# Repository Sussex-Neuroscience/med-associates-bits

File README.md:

# Med Associates open source add ons and bits

 Med Associates sells a number of tools for behavioural systems. This commercial system is a complete solution for behavioural experiments, and can be used to run multiple behavioural boxes in parallel. It is unfortunately rather expensive and closed source, so users are almost always dependent on MedAssociates for upgrades and customization (and whenever something breaks). Another downside is that an unusual 28V system is employed, so adding/customizing things has an extra layer of complexity.

 This repository is a collection of bits, add-ons and some knowledge on the system we have gathered over the years.
 
### [License](./LICENSE)

### [Code of Conduct](./code_of_conduct.md)

### [Contributing](./contributing.md)

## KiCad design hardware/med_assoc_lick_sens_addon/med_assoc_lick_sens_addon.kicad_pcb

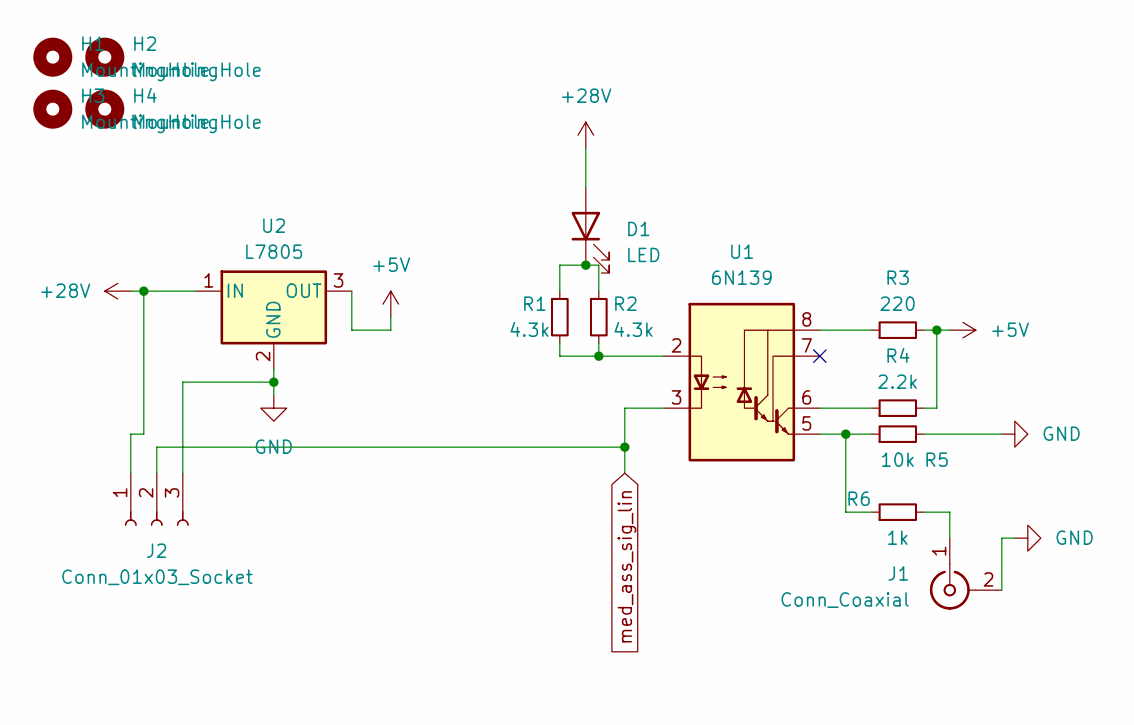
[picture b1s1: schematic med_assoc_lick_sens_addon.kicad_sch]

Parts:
D1: LED; LED_D5.0mm
H1, H2, H3, H4: MountingHole; MountingHole_3.2mm_M3
J1: Conn_Coaxial; TerminalBlock_Altech_AK300-2_P5.00mm
J2: Conn_01x03_Socket; TerminalBlock_Altech_AK300-3_P5.00mm
R1, R2: 4.3k; R_Axial_DIN0309_L9.0mm_D3.2mm_P12.70mm_Horizontal
R3: 220; R_Axial_DIN0309_L9.0mm_D3.2mm_P12.70mm_Horizontal
R4: 2.2k; R_Axial_DIN0309_L9.0mm_D3.2mm_P12.70mm_Horizontal
R5: 10k; R_Axial_DIN0309_L9.0mm_D3.2mm_P12.70mm_Horizontal
R6: 1k; R_Axial_DIN0309_L9.0mm_D3.2mm_P12.70mm_Horizontal
U1: 6N139; DIP-8_W7.62mm_LongPads
U2: L7805; TO-220-3_Vertical

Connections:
+5V: R3.2, R4.2, U2.3 (OUT)
+28V: D1.2 (A), J2.1, U2.1 (IN)
GND: J1.2 (Ext), J2.3, R5.2, U2.2 (GND)
unnamed: D1.1 (K), R1.1, R2.1
unnamed: J1.1 (In), R6.2
unnamed: R1.2, R2.2, U1.2 (C1)
unnamed: R5.1, R6.1, U1.5 (GND)
unnamed: R3.1, U1.8 (VCC)
unnamed: R4.1, U1.6 (VO2)
med_ass_sig_lin: J2.2, U1.3 (C2)

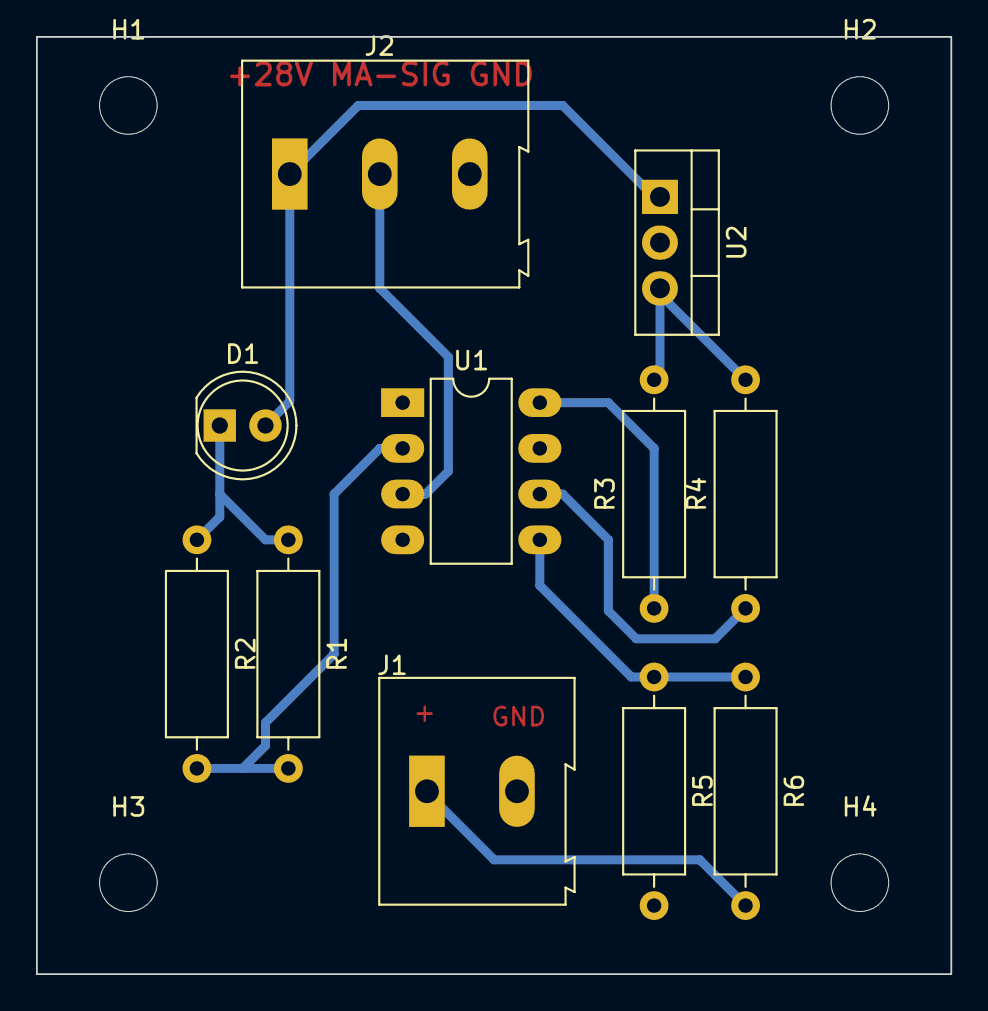
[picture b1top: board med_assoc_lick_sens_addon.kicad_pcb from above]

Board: 2 copper layers, 50.8 x 52.1 mm, 15 parts (0 on the bottom side), 10 nets.

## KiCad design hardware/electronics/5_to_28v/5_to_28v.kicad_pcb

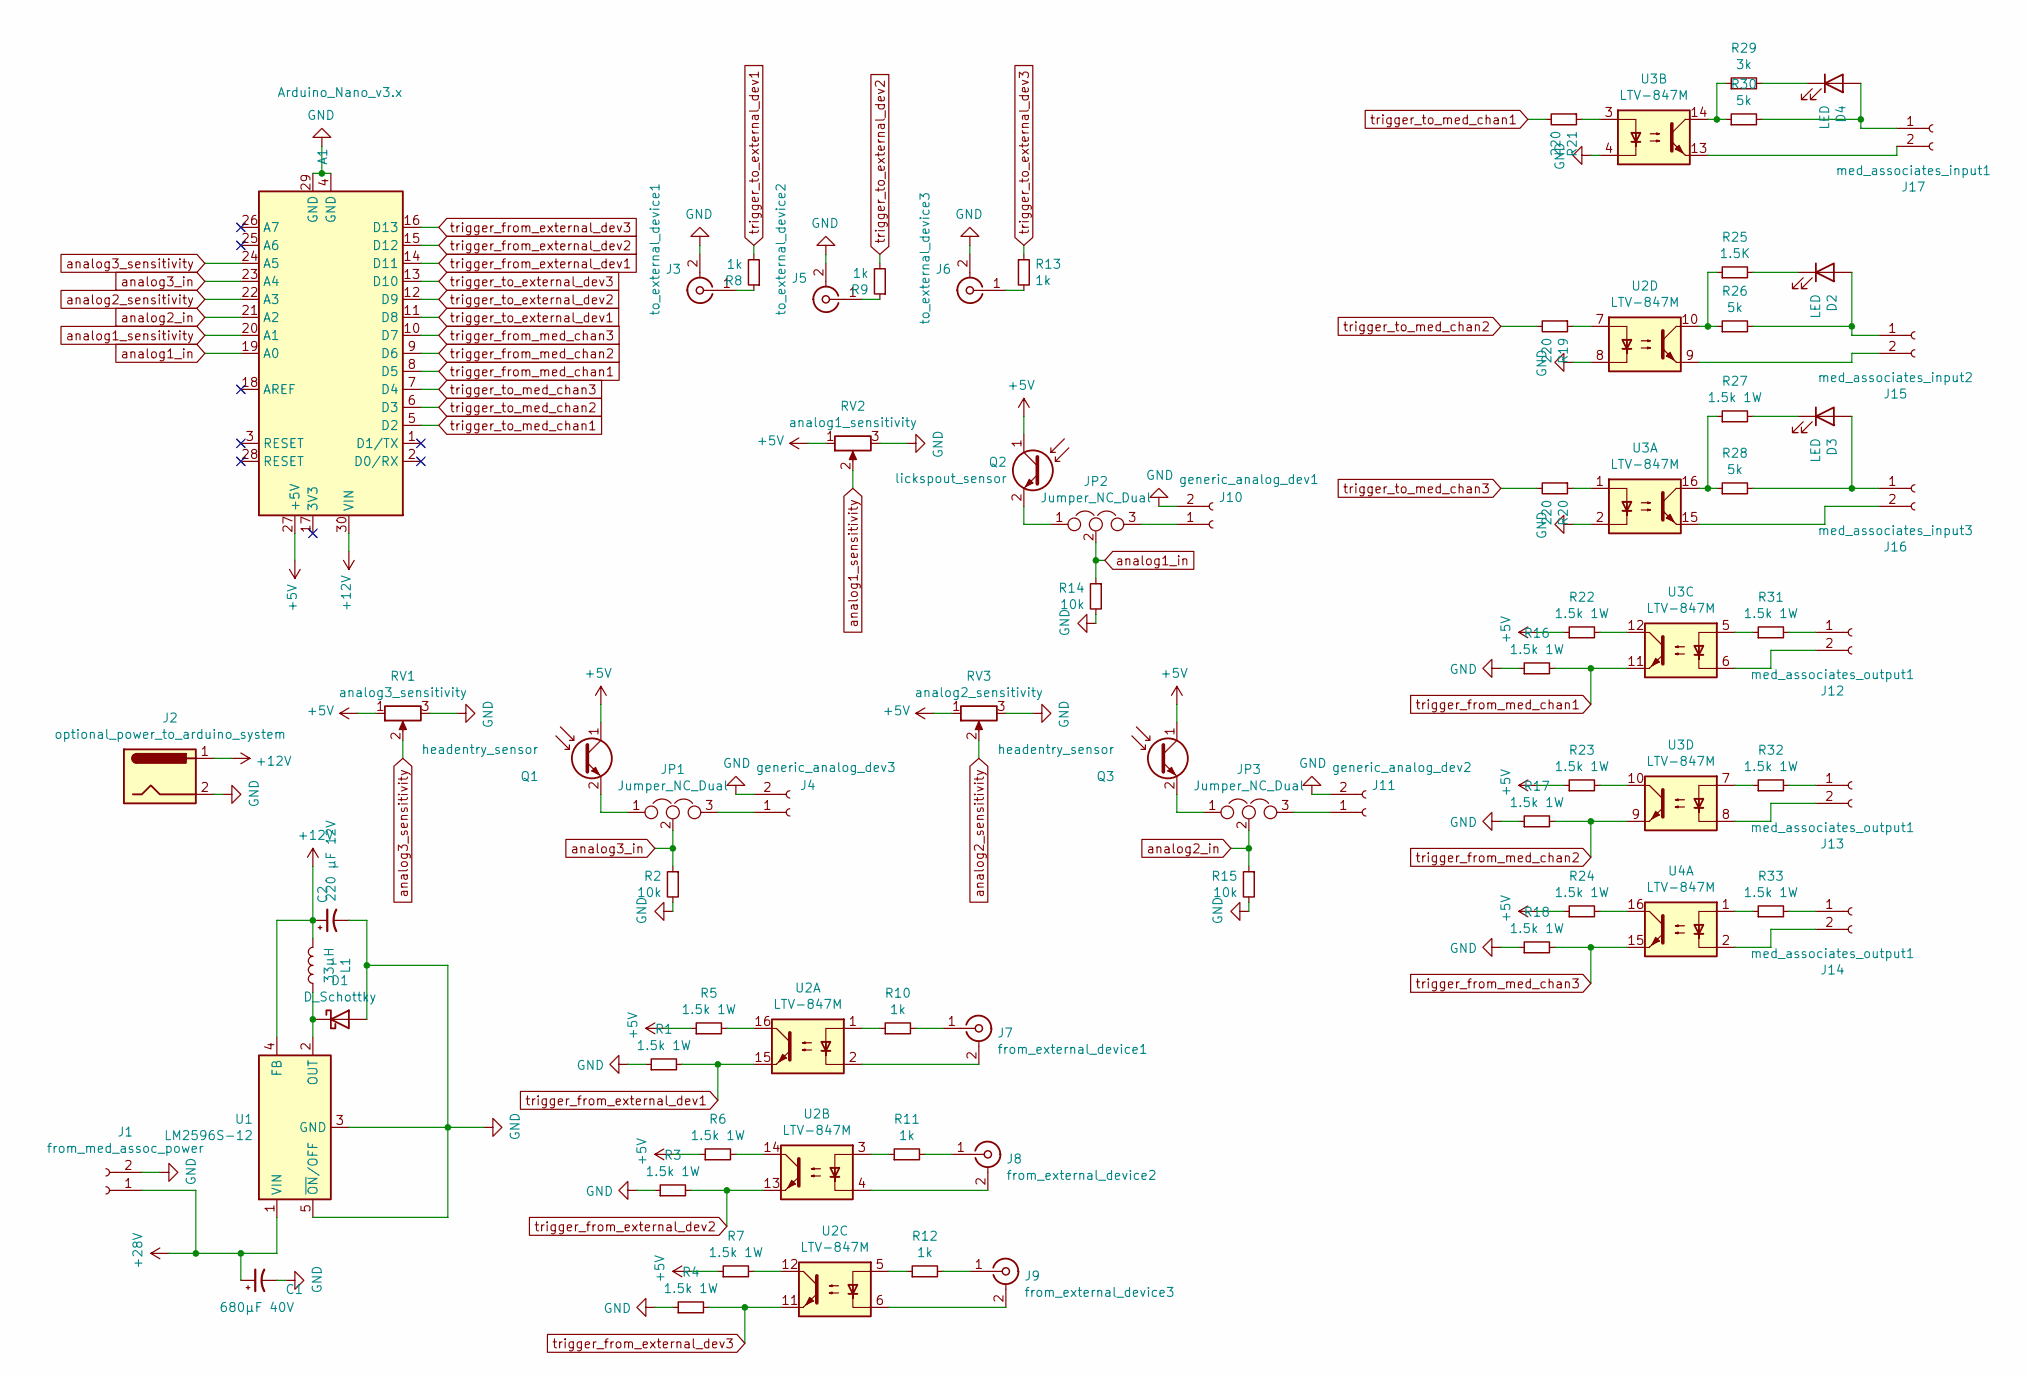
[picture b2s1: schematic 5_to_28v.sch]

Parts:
A1: Arduino_Nano_v3.x; Arduino_Nano
C1: 680µF 40V; CP_Radial_D10.0mm_P5.00mm_P7.50mm
C2: 220 µF 12V; CP_Radial_D10.0mm_P5.00mm_P7.50mm
D1: D_Schottky; D_DO-27_P15.24mm_Horizontal
D2, D3, D4: LED; LED_D5.0mm
J1: from_med_assoc_power; JST_XH_B2B-XH-A_1x02_P2.50mm_Vertical
J2: optional_power_to_arduino_system; BarrelJack_Horizontal
J3: to_external_device1; JST_XH_B2B-XH-A_1x02_P2.50mm_Vertical
J4: generic_analog_dev3; JST_XH_B2B-XH-A_1x02_P2.50mm_Vertical
J5: to_external_device2; JST_XH_B2B-XH-A_1x02_P2.50mm_Vertical
J6: to_external_device3; JST_XH_B2B-XH-A_1x02_P2.50mm_Vertical
J7: from_external_device1; JST_XH_B2B-XH-A_1x02_P2.50mm_Vertical
J8: from_external_device2; JST_XH_B2B-XH-A_1x02_P2.50mm_Vertical
J9: from_external_device3; JST_XH_B2B-XH-A_1x02_P2.50mm_Vertical
J10: generic_analog_dev1; JST_XH_B2B-XH-A_1x02_P2.50mm_Vertical
J11: generic_analog_dev2; JST_XH_B2B-XH-A_1x02_P2.50mm_Vertical
J12, J13, J14: med_associates_output1; JST_XH_B2B-XH-A_1x02_P2.50mm_Vertical
J15: med_associates_input2; JST_XH_B2B-XH-A_1x02_P2.50mm_Vertical
J16: med_associates_input3; JST_XH_B2B-XH-A_1x02_P2.50mm_Vertical
J17: med_associates_input1; JST_XH_B2B-XH-A_1x02_P2.50mm_Vertical
JP1, JP2, JP3: Jumper_NC_Dual; PinHeader_1x03_P2.54mm_Vertical
L1: 33µH; L_Radial_D7.5mm_P3.50mm_Fastron_07P
Q1, Q3: headentry_sensor; LED_D5.0mm
Q2: lickspout_sensor; LED_D5.0mm
R1, R3, R4, R5, R6, R7, R16, R17, R18, R22, R23, R24, R27, R31, R32, R33: 1.5k 1W; R_Axial_DIN0516_L15.5mm_D5.0mm_P25.40mm_Horizontal
R2, R14, R15: 10k; R_Axial_DIN0516_L15.5mm_D5.0mm_P25.40mm_Horizontal
R8, R9, R10, R11, R12, R13: 1k; R_Axial_DIN0411_L9.9mm_D3.6mm_P15.24mm_Horizontal
R19, R20, R21: 220; R_Axial_DIN0411_L9.9mm_D3.6mm_P15.24mm_Horizontal
R25: 1.5K; R_Axial_DIN0516_L15.5mm_D5.0mm_P25.40mm_Horizontal
R26, R28, R30: 5k; R_Axial_DIN0516_L15.5mm_D5.0mm_P25.40mm_Horizontal
R29: 3k; R_Axial_DIN0516_L15.5mm_D5.0mm_P25.40mm_Horizontal
RV1: analog3_sensitivity; JST_XH_B3B-XH-A_1x03_P2.50mm_Vertical
RV2: analog1_sensitivity; JST_XH_B3B-XH-A_1x03_P2.50mm_Vertical
RV3: analog2_sensitivity; JST_XH_B3B-XH-A_1x03_P2.50mm_Vertical
U1: LM2596S-12; TO-220-5_P3.4x3.7mm_StaggerOdd_Lead3.8mm_Vertical
U2, U3, U4: LTV-847M; DIP-16_W10.16mm

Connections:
+5V: A1.27 (+5V), Q1.1 (C), Q2.1 (C), Q3.1 (C), R5.1, R6.1, R7.1, R22.1, R23.1, R24.1, RV1.1, RV2.1, RV3.1
+12V: A1.30 (VIN), C2.1, J2.1, L1.2, U1.4 (FB)
+28V: C1.1, J1.1, U1.1 (VIN)
GND: A1.4 (GND), A1.29 (GND), C1.2, C2.2, D1.2 (A), J1.2, J2.2, J3.2 (Ext), J4.2, J5.2 (Ext), J6.2 (Ext), J10.2, J11.2, R1.1, R2.2, R3.1, R4.1, R14.2, R15.2, R16.1, R17.1, R18.1, RV1.3, RV2.3, RV3.3, U1.3 (GND), U1.5 (~ON~/OFF), U2.8, U3.2, U3.4
unnamed: D1.1 (K), L1.1, U1.2 (OUT)
unnamed: D2.1 (K), R25.2
unnamed: D2.2 (A), J15.1, R26.2
unnamed: D3.1 (K), R27.2
unnamed: D3.2 (A), J16.1, R28.2
unnamed: D4.1 (K), R29.2
unnamed: D4.2 (A), J17.1, R30.2
unnamed: J3.1 (In), R8.1
unnamed: J4.1, JP1.3
unnamed: J5.1 (In), R9.1
unnamed: J6.1 (In), R13.2
unnamed: J7.1 (In), R10.2
unnamed: J7.2 (Ext), U2.2
unnamed: J8.1 (In), R11.2
unnamed: J8.2 (Ext), U2.4
unnamed: J9.1 (In), R12.2
unnamed: J9.2 (Ext), U2.6
unnamed: J10.1, JP2.3
unnamed: J11.1, JP3.3
unnamed: J12.1, R31.2
unnamed: J12.2, U3.6
unnamed: J13.1, R32.2
unnamed: J13.2, U3.8
unnamed: J14.1, R33.2
unnamed: J14.2, U4.2
unnamed: J15.2, U2.9
unnamed: J16.2, U3.15
unnamed: J17.2, U3.13
unnamed: JP1.1, Q1.2 (E)
unnamed: JP2.1, Q2.2 (E)
unnamed: JP3.1, Q3.2 (E)
unnamed: R5.2, U2.16
unnamed: R6.2, U2.14
unnamed: R7.2, U2.12
unnamed: R10.1, U2.1
unnamed: R11.1, U2.3
unnamed: R12.1, U2.5
unnamed: R19.1, U2.7
unnamed: R20.1, U3.1
unnamed: R21.1, U3.3
unnamed: R22.2, U3.12
unnamed: R23.2, U3.10
unnamed: R24.2, U4.16
unnamed: R25.1, R26.1, U2.10
unnamed: R27.1, R28.1, U3.16
unnamed: R29.1, R30.1, U3.14
unnamed: R31.1, U3.5
unnamed: R32.1, U3.7
unnamed: R33.1, U4.1
analog1_in: A1.19 (A0), JP2.2, R14.1
analog1_sensitivity: A1.20 (A1), RV2.2
analog2_in: A1.21 (A2), JP3.2, R15.1
analog2_sensitivity: A1.22 (A3), RV3.2
analog3_in: A1.23 (A4), JP1.2, R2.1
analog3_sensitivity: A1.24 (A5), RV1.2
trigger_from_external_dev1: A1.14 (D11), R1.2, U2.15
trigger_from_external_dev2: A1.15 (D12), R3.2, U2.13
trigger_from_external_dev3: A1.16 (D13), R4.2, U2.11
trigger_from_med_chan1: A1.8 (D5), R16.2, U3.11
trigger_from_med_chan2: A1.9 (D6), R17.2, U3.9
trigger_from_med_chan3: A1.10 (D7), R18.2, U4.15
trigger_to_external_dev1: A1.11 (D8), R8.2
trigger_to_external_dev2: A1.12 (D9), R9.2
trigger_to_external_dev3: A1.13 (D10), R13.1
trigger_to_med_chan1: A1.5 (D2), R21.2
trigger_to_med_chan2: A1.6 (D3), R19.2
trigger_to_med_chan3: A1.7 (D4), R20.2

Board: 2 copper layers, 71 parts (0 on the bottom side), 71 nets, no tracks yet.

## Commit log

2019-10-29 developing a licking spout port. mechanics
2019-10-29 more testing with licking spout
2019-11-04 add bits and bops that will help the behavioural box
2019-11-25 changed the electronics schematics for the 5to28V converter, created the licking spout for animals implanted with photometry fibers and made a printed part to subsitute a plexiglass grid holder that 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
2019-11-29 Update analog_to_digital.ino
    so that two led indicators are reporting the animal's interaction with the device.
2019-12-29 add changesto arduino and hardware
2020-01-01 updated comments on arduino code
2020-01-01 update root readme, by adding information about the project and links to license, code of conduct, contributing
2020-01-01 update readme.md with information about building
2020-01-02 remove related work file and update building instructions
2020-01-13 clean up repository
2020-08-03 add baords and updates to code
2020-08-11 first implementation of a generic solution
2023-03-06 add plates design
2023-03-06 rename and update repo to be more of a general system to deposit med-ass info
2023-07-12 create schematics and pcb for lick sensor addon
2023-07-13 move traces to bottom side of board
2023-07-17 update traces and other bits
2023-08-15 create CNC paths for carvera
